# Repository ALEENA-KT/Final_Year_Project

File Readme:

#DESIGN AND DEVELOPMENT OF 5KW MODULAR GRID CONNECTED CONVERTER
The primary objective of this project is to develop and implement a state-of-the-art
5KW modular grid-connected converter with the goal of revolutionizing energy conver-
sion systems for increased adaptability and efficiency. In a grid-connected environment,
the converter’s function is to control source power, making it compatible with a range
of load requirements. The converter’s modular design offers a scalable and adaptable
method that enables easy integration into a range of power systems. Because of its
versatility and 5KW capacity, it can be used in both residential and commercial envi-
ronments. The focus on modularity makes it simple to expand or reconfigure to meet
changing energy requirements.
This project report addresses the imperative control objectives of a three-phase
(3Phase) active front end (AFE) converter, aiming to achieve enhanced performance
in line with IEEE standards. The identified control objectives include maintaining a
low value for line current Total Harmonic Distortion (THD) at the AC side (THDi less
than or equal to 5 Percentage), ensuring in-phase operation of AC side voltages and
currents, and achieving superior regulation of the DC link voltage.
In energy processing, pulse width modulation (PWM) techniques are essential for
producing accurate gate signals for power semiconductor devices. This guarantees the
best possible power conversion efficiency and performance. This project pushes the
limits of innovation in energy conversion technology by building upon a wealth of
research in semiconductor devices, converter topologies, PWM techniques, and con-
trollers. With its ability to handle the dynamic challenges of modern power systems
and its contribution to the ongoing evolution of smart grids and renewable energy in-
tegration, the 5KW modular grid-connected converter is a significant milestone in the
search for sustainable and flexible energy solutions

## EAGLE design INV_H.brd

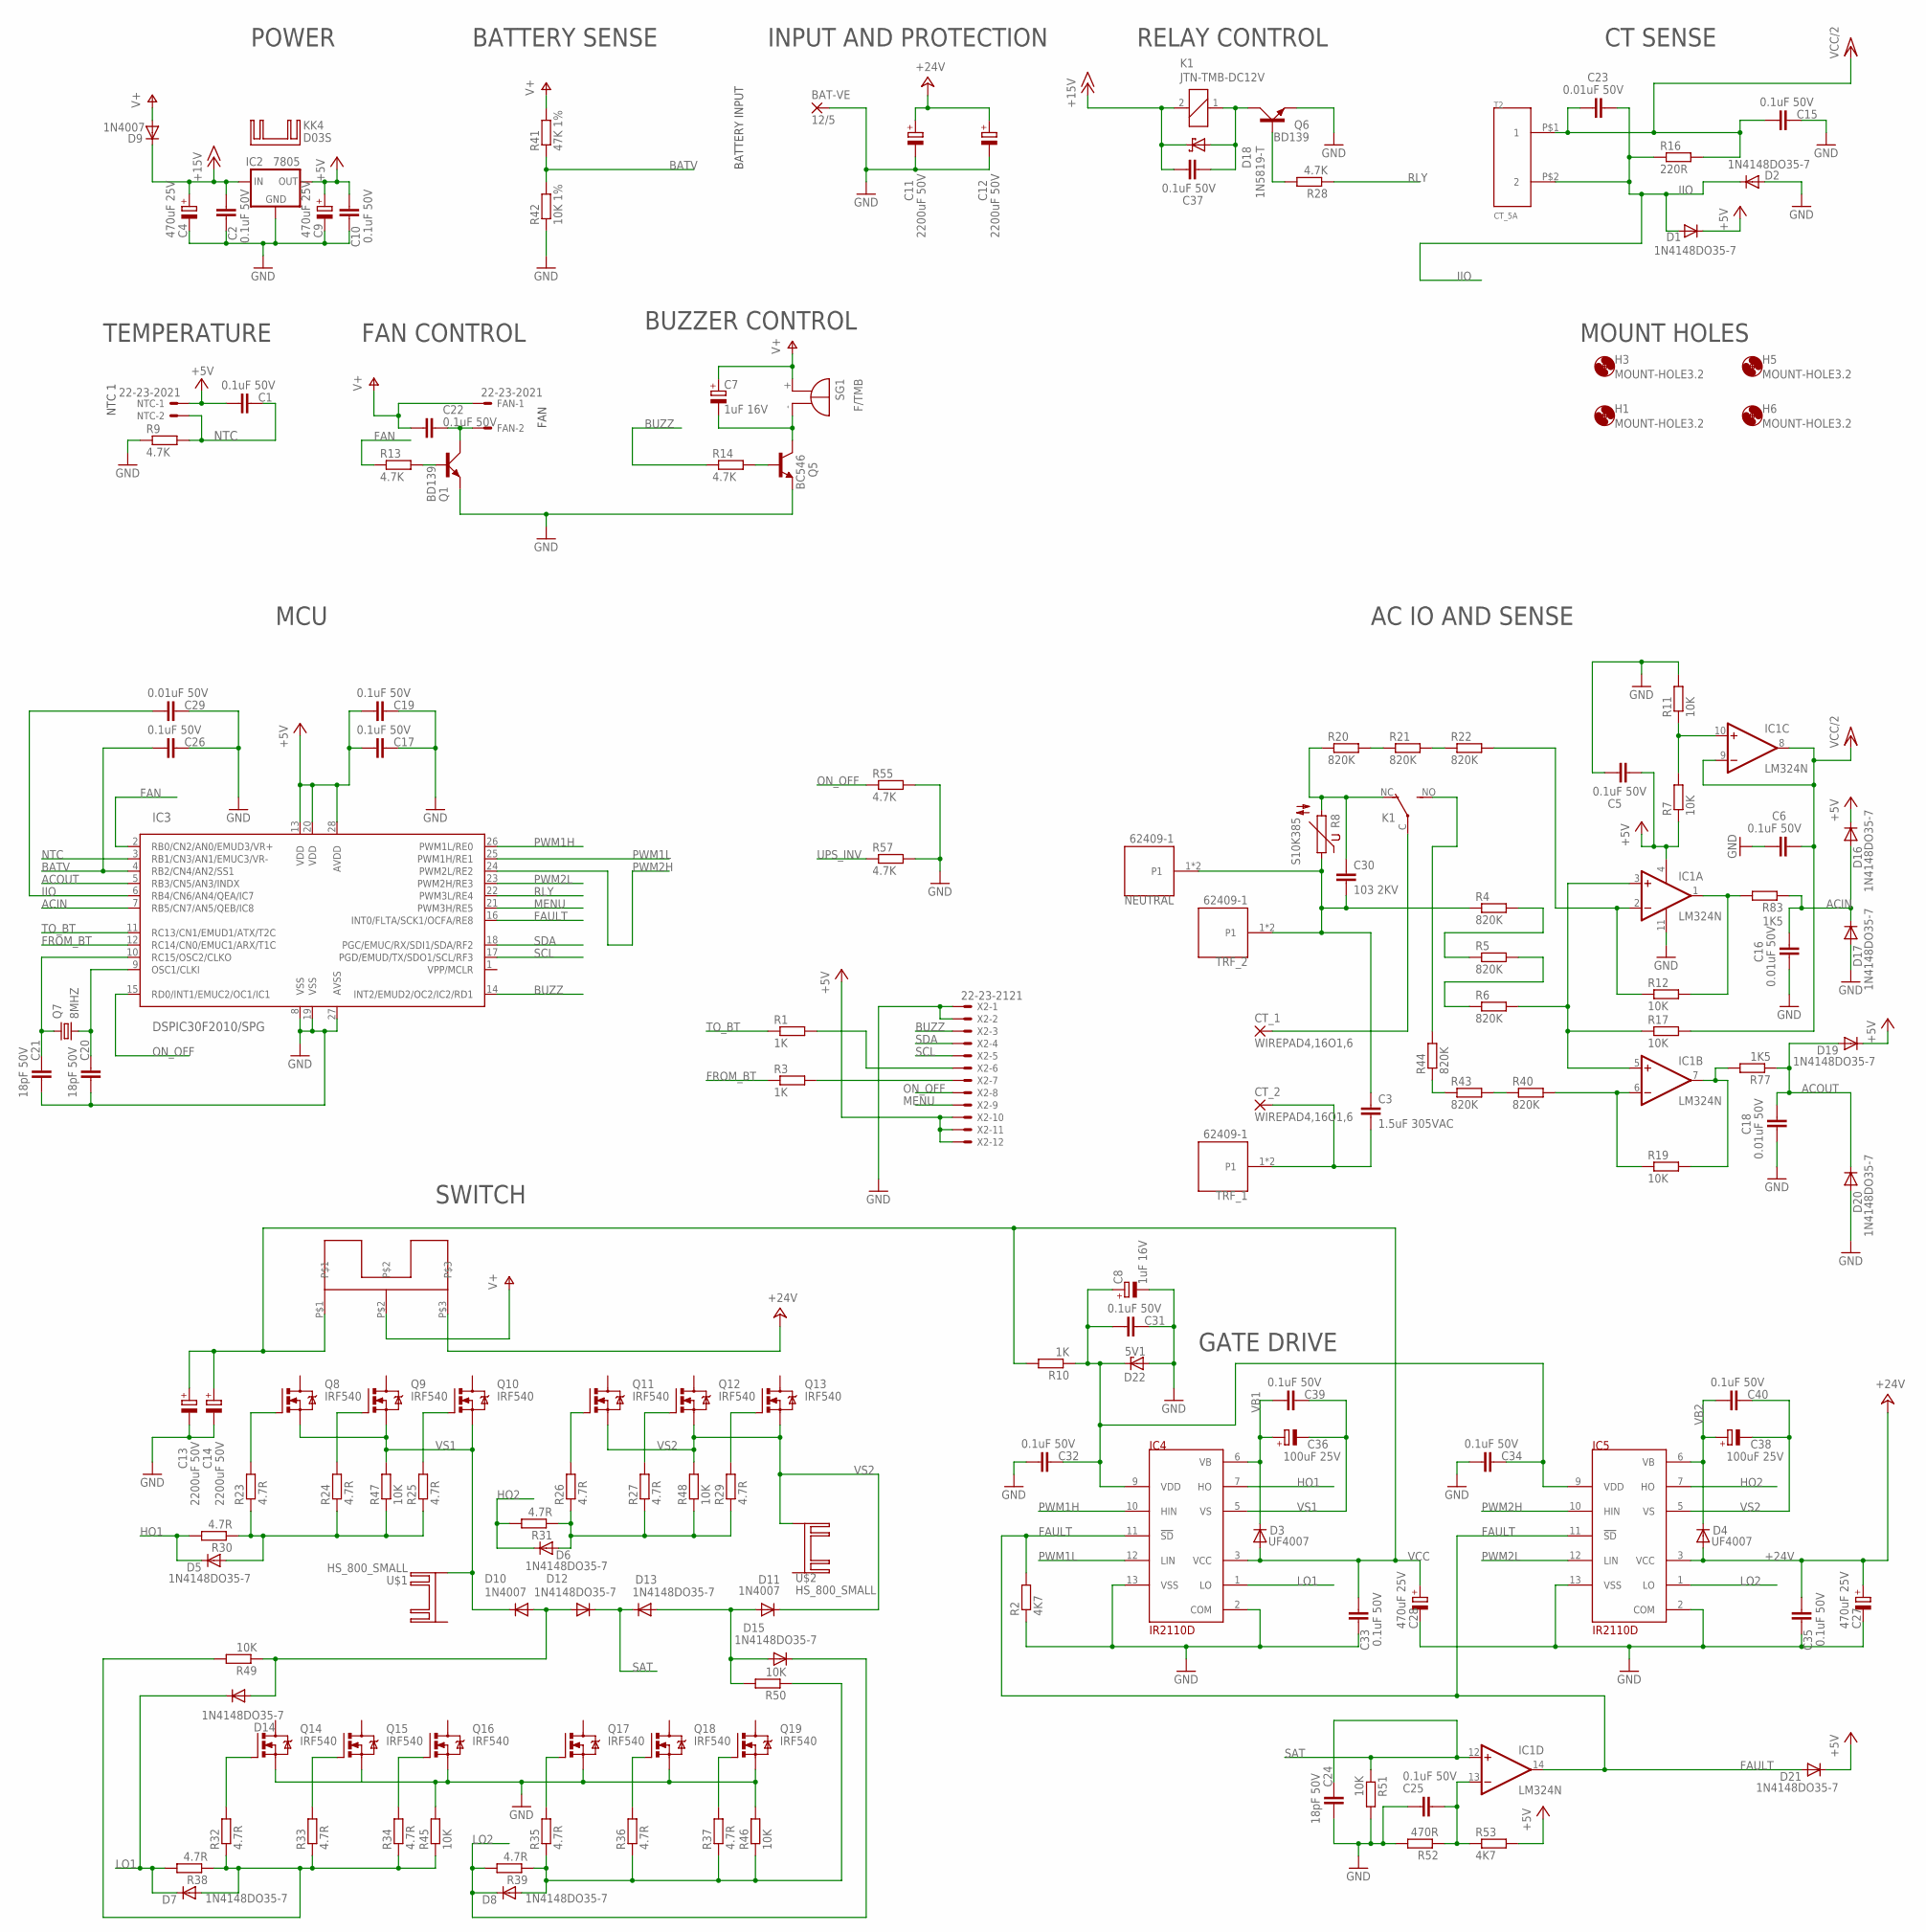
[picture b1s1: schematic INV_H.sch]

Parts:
BAT-VE: 12/5; 8/5
C1, C2, C5, C6, C10, C15, C17, C19, C22, C25, C26, C31, C32, C33, C34, C35, C37, C39, C40: 0.1uF 50V; C025-025X050
C3: 1.5uF 305VAC; C275-113X316
C4, C9, C27, C28: 470uF 25V; E3,5-8
C7, C8: 1uF 16V; E1,8-4
C11, C12, C13, C14: 2200uF 50V; E7,5-16
C16, C18, C23, C29: 0.01uF 50V; C025-025X050
C20, C21, C24: 18pF 50V; C025-025X050
C30: 103 2KV; C075-032X103
C36, C38: 100uF 25V; E2,5-6
CT_1, CT_2: WIREPAD4,16O1,6; 4,16O1,6
D1, D2, D5, D6, D7, D8, D12, D13, D14, D15, D16, D17, D19, D20, D21: 1N4148DO35-7; DO35-7
D3, D4: UF4007; DO41-10
D9, D10, D11: 1N4007; DO41-10
D18: 1N5819-T; DO41-7.6
D22: 5V1; DO34Z7
FAN: 22-23-2021
H1, H3, H5, H6: MOUNT-HOLE3.2; 3,2
IC1: LM324N; DIL14
IC2: 7805; 78XXS
IC3: DSPIC30F2010/SPG; DIL28-3
IC4, IC5: IR2110D; DIL14
K1: JTN-TMB-DC12V; JT-TMB
KK4: D03S
KK5: HS_800_BIG; 800W_BIG
NEUTRAL: 62409-1; TE_62409-1
NTC: 22-23-2021
Q1, Q6: BD139; TO126AV
Q5: BC546; TO92-EBC
Q7: 8MHZ; HC49/S
Q8, Q9, Q10, Q11, Q12, Q13, Q14, Q15, Q16, Q17, Q18, Q19: IRF540; TO220BV
R1, R3, R10: 1K; 0204/7
R2, R53: 4K7; 0204/7
R4, R5, R6, R20, R21, R22, R40, R43, R44: 820K; 0204/7
R7, R11, R12, R17, R19, R45, R46, R47, R48, R49, R50, R51: 10K; 0204/7
R8: S10K385
R9, R13, R14, R28, R55, R57: 4.7K; 0204/7
R16: 220R; 0204/7
R23, R24, R25, R26, R27, R29, R30, R31, R32, R33, R34, R35, R36, R37, R38, R39: 4.7R; 0204/7
R41: 47K 1%; 0204/7
R42: 10K 1%; 0204/7
R52: 470R; 0204/7
R77, R83: 1K5; 0204/7
SG1: F/TMB
T2: CT_5A
TRF_1, TRF_2: 62409-1; TE_62409-1
U$1, U$2: HS_800_SMALL; 800W_SMALL
X2: 22-23-2121

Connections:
+5V: C1.2, C5.2, C9.+, C10.2, C17.2, C19.2, D1.C, D16.C, D19.C, D21.C, IC1.4 (V+), IC2.OUT, IC3.13 (VDD), IC3.20 (VDD), IC3.28 (AVDD), NTC.1, R7.3 (1), R53.4 (2), X2.10, X2.11, X2.12
+15V: C2.2, C4.+, C37.1, D9.C, D18.C, IC2.IN, K1.2
+24V: C11.+, C12.+, C27.+, C35.2, D4.A, IC5.3 (VCC), KK5.P$3
ACIN: C16.1, D16.A, D17.C, IC3.7 (RB5/CN7/AN5/QEB/IC8), R83.3 (1)
ACOUT: C18.1, D19.A, D20.C, IC3.5 (RB3/CN5/AN3/INDX), R77.3 (1)
BATV: C26.2, IC3.4 (RB2/CN4/AN2/SS1), R41.3 (1), R42.4 (2)
BUZZ: IC3.14 (INT2/EMUD2/OC2/IC2/RD1), R14.3 (1), X2.3
FAN: IC3.2 (RB0/CN2/AN0/EMUD3/VR+), R13.3 (1)
FAULT: D21.A, IC1.14 (OUT), IC3.16 (INT0/FLTA/SCK1/OCFA/RE8), IC4.11 (!SD), IC5.11 (!SD), R2.4 (2)
FROM_BT: IC3.12 (RC14/CN0/EMUC1/ARX/T1C), R3.3 (1)
GND: BAT-VE.P$1, C2.1, C4.-, C5.1, C6.2, C8.-, C9.-, C10.1, C11.-, C12.-, C13.-, C14.-, C15.1, C16.2, C17.1, C18.2, C19.1, C20.2, C21.2, C24.2, C25.2, C26.1, C27.-, C28.-, C29.1, C31.1, C32.2, C33.1, C34.2, C35.1, D2.A, D17.A, D20.A, D22.A, IC1.11 (V-), IC2.GND, IC3.8 (VSS), IC3.19 (VSS), IC3.27 (AVSS), IC4.2 (COM), IC4.13 (VSS), IC5.2 (COM), IC5.13 (VSS), Q1.E, Q5.E, Q6.E, Q14.S, Q15.S, Q16.S, Q17.S, Q18.S, Q19.S, R2.3 (1), R9.3 (1), R11.4 (2), R42.3 (1), R45.4 (2), R46.4 (2), R51.4 (2), R52.4 (2), R55.4 (2), R57.4 (2), X2.1, X2.2
HO1: D5.C, IC4.7 (HO), R30.4 (2)
HO2: D6.C, IC5.7 (HO), R31.4 (2)
IIO: C23.1, C29.2, D1.A, D2.C, IC3.6 (RB4/CN6/AN4/QEA/IC7), R16.3 (1), T2.P$2 (2)
LO1: D7.C, D14.C, IC4.1 (LO), R38.4 (2)
LO2: D8.C, D15.C, IC5.1 (LO), R39.4 (2)
MENU: IC3.21 (PWM3H/RE5), X2.9
unnamed: C3.1, C30.2, NEUTRAL.1, NEUTRAL.2, R4.3 (1), R8.1, TRF_2.1, TRF_2.2
unnamed: R3.4 (2), X2.7
unnamed: C3.2, CT_2.1, TRF_1.1, TRF_1.2
unnamed: CT_1.1, K1.C
unnamed: C30.1, K1.NC (O), R8.2, R20.3 (1)
unnamed: C25.1, IC1.13 (-IN), R52.3 (1), R53.3 (1)
unnamed: IC1.10 (+IN), R7.4 (2), R11.3 (1)
unnamed: R4.4 (2), R5.3 (1)
unnamed: C22.1, FAN.2, Q1.C
unnamed: Q1.B, R13.4 (2)
unnamed: C7.-, Q5.C, SG1.-
unnamed: Q5.B, R14.4 (2)
unnamed: R5.4 (2), R6.3 (1)
unnamed: C20.1, IC3.9 (OSC1/CLKI), Q7.2
unnamed: IC1.3 (+IN), IC1.5 (+IN), R6.4 (2), R17.3 (1)
unnamed: C21.1, IC3.10 (RC15/OSC2/CLKO), Q7.1
unnamed: IC1.2 (-IN), R12.3 (1), R22.4 (2)
unnamed: D10.A, D12.A, D14.A, R49.3 (1)
unnamed: IC1.6 (-IN), R19.3 (1), R40.4 (2)
unnamed: R20.4 (2), R21.3 (1)
unnamed: R21.4 (2), R22.3 (1)
unnamed: K1.NO (S), R44.4 (2)
unnamed: R43.3 (1), R44.3 (1)
unnamed: Q8.G, R23.4 (2)
unnamed: Q9.G, R24.4 (2)
unnamed: Q10.G, R25.4 (2)
unnamed: D5.A, R23.3 (1), R24.3 (1), R25.3 (1), R30.3 (1), R47.3 (1)
unnamed: R40.3 (1), R43.4 (2)
unnamed: D7.A, R32.3 (1), R33.3 (1), R34.3 (1), R38.3 (1), R45.3 (1), R49.4 (2)
unnamed: Q14.G, R32.4 (2)
unnamed: Q15.G, R33.4 (2)
unnamed: Q16.G, R34.4 (2)
unnamed: Q11.G, R26.4 (2)
unnamed: D6.A, R26.3 (1), R27.3 (1), R29.3 (1), R31.3 (1), R48.3 (1)
unnamed: D8.A, R35.3 (1), R36.3 (1), R37.3 (1), R39.3 (1), R46.3 (1), R50.3 (1)
unnamed: C37.2, D18.A, K1.1, Q6.C
unnamed: Q17.G, R35.4 (2)
unnamed: Q6.B, R28.4 (2)
unnamed: Q18.G, R36.4 (2)
unnamed: Q19.G, R37.4 (2)
unnamed: Q13.G, R29.4 (2)
unnamed: Q12.G, R27.4 (2)
unnamed: D11.A, D13.A, D15.A, R50.4 (2)
unnamed: R1.4 (2), X2.6
unnamed: IC1.7 (OUT), R19.4 (2), R77.4 (2)
unnamed: IC1.1 (OUT), R12.4 (2), R83.4 (2)
NTC: C1.1, IC3.3 (RB1/CN3/AN1/EMUC3/VR-), NTC.2, R9.4 (2)
ON_OFF: IC3.15 (RD0/INT1/EMUC2/OC1/IC1), R55.3 (1), X2.8
PWM1H: IC3.26 (PWM1L/RE0), IC4.10 (HIN)
PWM1L: IC3.25 (PWM1H/RE1), IC4.12 (LIN)
PWM2H: IC3.24 (PWM2L/RE2), IC5.10 (HIN)
PWM2L: IC3.23 (PWM2H/RE3), IC5.12 (LIN)
RLY: IC3.22 (PWM3L/RE4), R28.3 (1)
SAT: C24.1, D12.C, D13.C, IC1.12 (+IN), R51.3 (1)
SCL: IC3.17 (PGD/EMUD/TX/SDO1/SCL/RF3), X2.5
SDA: IC3.18 (PGC/EMUC/RX/SDI1/SDA/RF2), X2.4
TO_BT: IC3.11 (RC13/CN1/EMUD1/ATX/T2C), R1.3 (1)
UPS_INV: R57.3 (1)
V+: C7.+, C22.2, D9.A, FAN.1, KK5.P$2, R41.4 (2), SG1.+
VB1: C36.+, C39.2, D3.C, IC4.6 (VB)
VB2: C38.+, C40.2, D4.C, IC5.6 (VB)
VCC: C13.+, C14.+, C28.+, C33.2, D3.A, IC4.3 (VCC), KK5.P$1, R10.4 (2)
VCC/2: C6.1, C15.2, C23.2, IC1.8 (OUT), IC1.9 (-IN), R16.4 (2), R17.4 (2), T2.P$1 (1)
VDD: C8.+, C31.2, C32.1, C34.1, D22.C, IC4.9 (VDD), IC5.9 (VDD), R10.3 (1)
VS1: C36.-, C39.1, D10.C, IC4.5 (VS), Q8.S, Q9.S, Q10.S, R47.4 (2), U$1.P$2
VS2: C38.-, C40.1, D11.C, IC5.5 (VS), Q11.S, Q12.S, Q13.S, R48.4 (2), U$2.P$1

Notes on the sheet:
POWER
INPUT AND PROTECTION
BATTERY INPUT
NTC 1
FAN
AC IO AND SENSE
GATE DRIVE
MCU
SWITCH
MOUNT HOLES
BATTERY SENSE
TEMPERATURE
FAN CONTROL
BUZZER CONTROL
RELAY CONTROL
CT SENSE

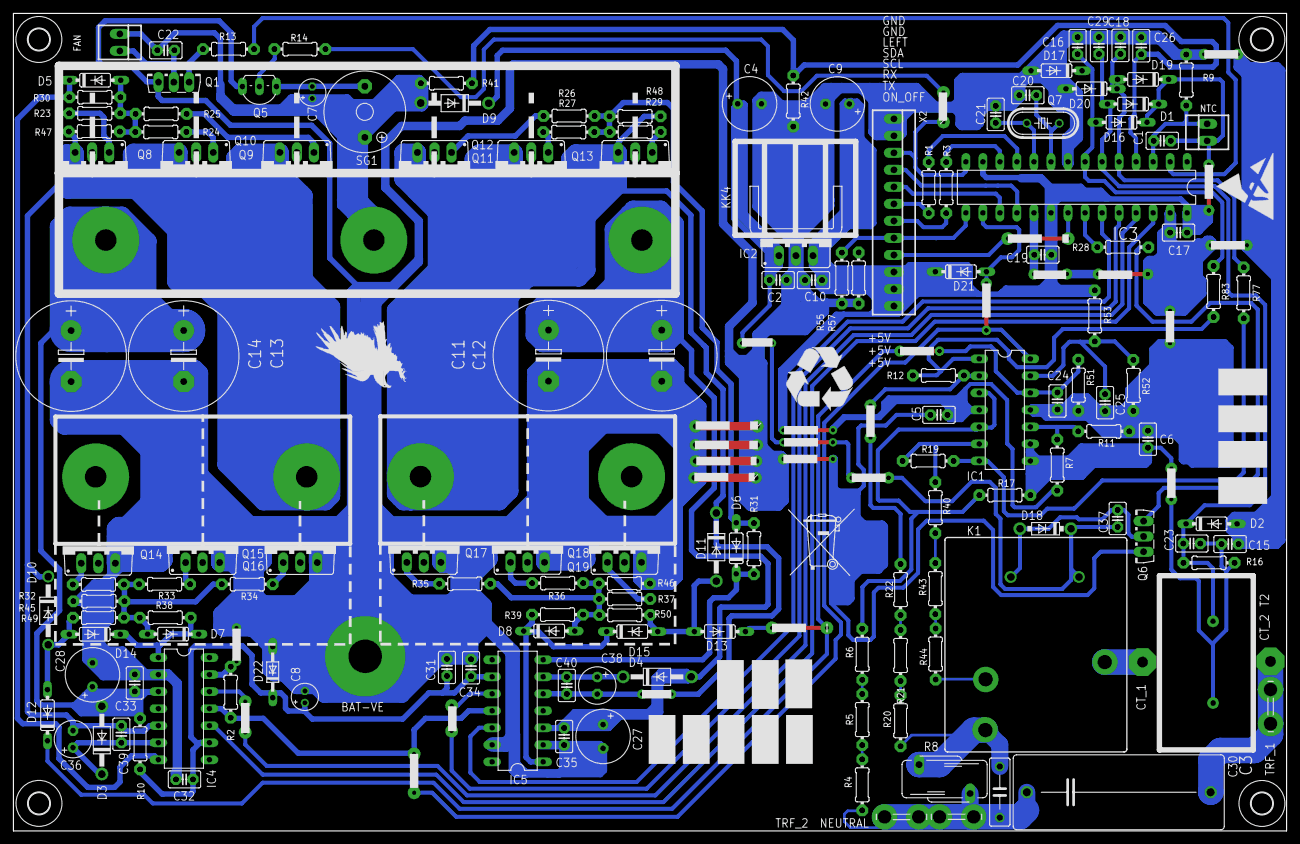
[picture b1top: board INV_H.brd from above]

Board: 2 copper layers, 190.0 x 122.0 mm, 162 parts (0 on the bottom side), 82 nets.

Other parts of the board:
U$3: ESD_10.00
U$4: MUELLTONNE_10.00
U$5: RECYCLING_10.00
U$6: EAGLE-PLC-10MM

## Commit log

2024-04-30 Uploaded simulation of fuzzylogic
